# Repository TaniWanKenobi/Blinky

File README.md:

# Blinky Board

Made by **@Tanishq Goyal**

## What is the Blinky Board?

The Blinky Board is a colorful LED chaser that you can customize with your own PCB art! It uses:

- **NE555 Timer IC** in astable mode to generate clock pulses
- **CD4017 Decade Counter IC** to drive 10 LEDs in sequence
- Resistors, capacitors, and a potentiometer to control timing
- A custom PCB you design in **KiCad** and manufacture via **JLCPCB**

## How can I make my own Blinky Board?

I made this to teach people how to make a blinking circuit! It can be found [here](blinkyguide.md)

Assembly instructions can be found [here](https://blueprint.hackclub.com/resources/blinky-assembly)

Submit this at [Blueprint](https://blueprint.hackclub.com/)!

## 3D Model

## PCB

## Schematic

## Components Used

- **NE555P** – Timer IC  
- **CD4017** – Decade Counter IC  
- **Resistors** – 1kΩ, 470Ω  
- **Potentiometer (RV)** – Variable resistor for speed control  
- **Capacitors** – Electrolytic & ceramic  
- **LEDs** – 10 total (red, orange, yellow, emerald, blue)  

## License
This project is licensed under the CERN Open Hardware Licence Version 2 - Strongly Reciprocal. See the [LICENSE](LICENSE) file for details.

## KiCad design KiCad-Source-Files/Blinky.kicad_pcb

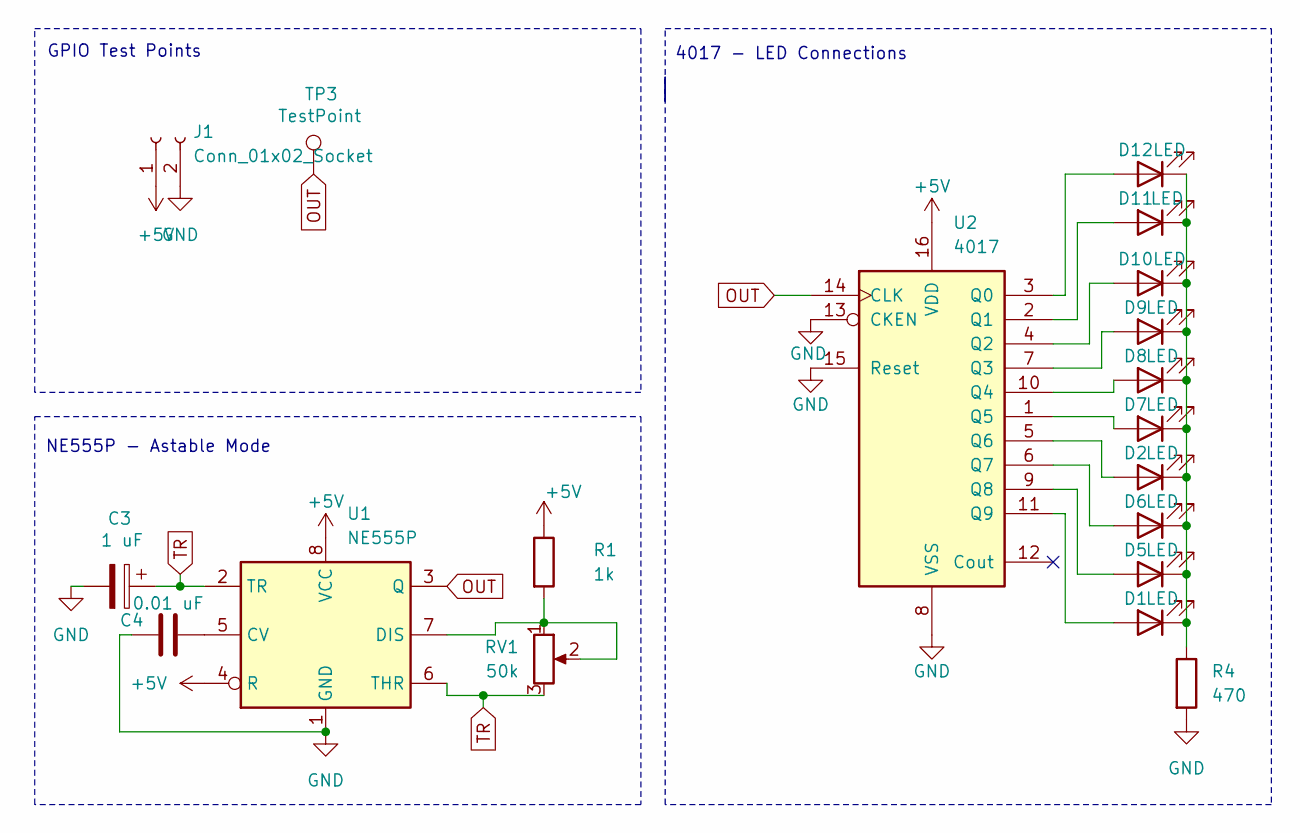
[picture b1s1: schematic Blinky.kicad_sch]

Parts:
C3: 1 uF; CP_Radial_D5.0mm_P2.00mm
C4: 0.01 uF; CP_Radial_D5.0mm_P2.00mm
D1, D2, D5, D6, D7, D8, D9, D10, D11, D12: LED; LED_D3.0mm
J1: Conn_01x02_Socket; PinHeader_1x02_P2.54mm_Vertical
R1: 1k; R_Axial_DIN0207_L6.3mm_D2.5mm_P7.62mm_Horizontal
R4: 470; R_Axial_DIN0207_L6.3mm_D2.5mm_P7.62mm_Horizontal
RV1: 50k; Potentiometer_Vishay_T93YA_Vertical
TP3: TestPoint; PinSocket_1x01_P2.54mm_Vertical
U1: NE555P; DIP-8_W7.62mm
U2: 4017; N16

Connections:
+5V: J1.1, R1.1, U1.4 (R), U1.8 (VCC), U2.16 (VDD)
GND: C3.2, C4.1, J1.2, R4.2, U1.1 (GND), U2.8 (VSS), U2.13 (CKEN), U2.15 (Reset)
unnamed: D1.2 (A), U2.11 (Q9)
unnamed: D1.1 (K), D2.1 (K), D5.1 (K), D6.1 (K), D7.1 (K), D8.1 (K), D9.1 (K), D10.1 (K), D11.1 (K), D12.1 (K), R4.1
unnamed: D2.2 (A), U2.5 (Q6)
unnamed: D5.2 (A), U2.9 (Q8)
unnamed: D6.2 (A), U2.6 (Q7)
unnamed: D7.2 (A), U2.1 (Q5)
unnamed: D8.2 (A), U2.10 (Q4)
unnamed: D9.2 (A), U2.7 (Q3)
unnamed: D10.2 (A), U2.4 (Q2)
unnamed: D11.2 (A), U2.2 (Q1)
unnamed: D12.2 (A), U2.3 (Q0)
unnamed: C4.2, U1.5 (CV)
unnamed: R1.2, RV1.1, RV1.2, U1.7 (DIS)
OUT: TP3.1, U1.3 (Q), U2.14 (CLK)
TR: C3.1, RV1.3, U1.2 (TR), U1.6 (THR)

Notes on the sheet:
GPIO Test Points
4017 - LED Connections
NE555P - Astable Mode

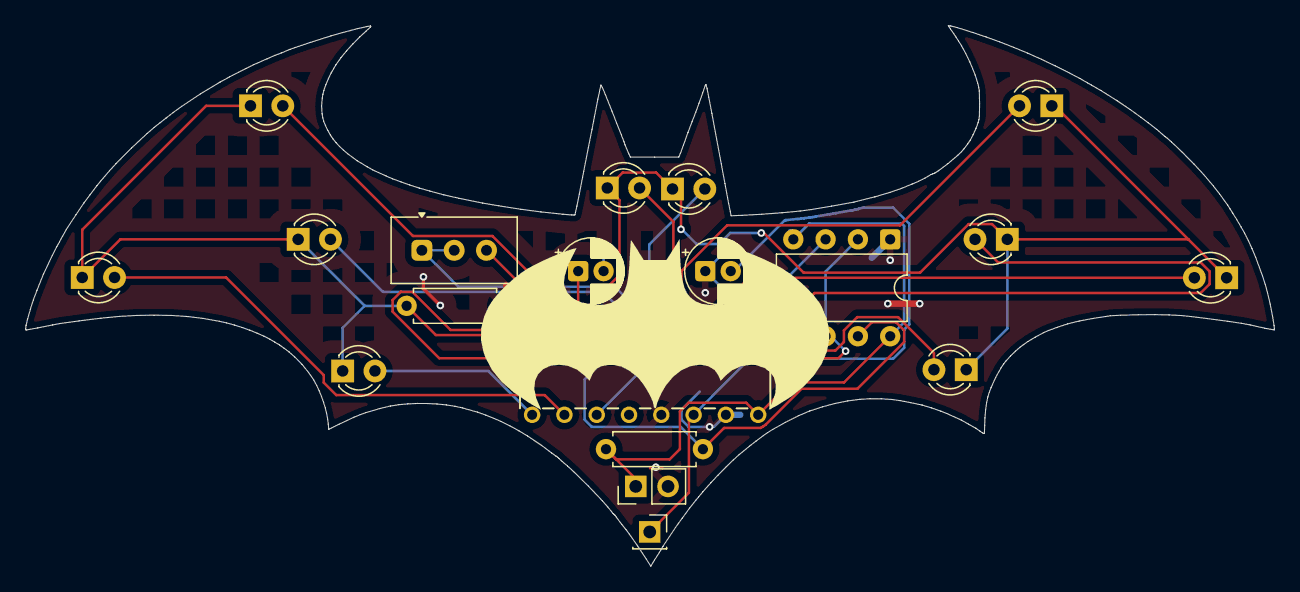
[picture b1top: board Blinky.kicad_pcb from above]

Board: 2 copper layers, 98.2 x 42.5 mm, 19 parts (0 on the bottom side), 17 nets.

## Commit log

2025-12-06 Add tutorial for building a 555 LED Chaser board
    This tutorial provides a comprehensive guide on building a 555 LED Chaser board, including setup, design, and submission processes.
2025-12-06 Document GPIO connection and resistor calculation
    Added instructions for connecting GPIO to LEDs and calculating resistor values.
2025-12-06 Clarify LED circuit parameters and resistor usage
    Added definitions for supply voltage, LED forward voltage, and desired current. Enhanced explanation of power-limiting resistors and their impact on LED brightness and component life.
2025-12-06 Improve LED connection instructions and resistor details
    Revised text for clarity and conciseness regarding LED connections and resistor values.
2025-12-07 Enhance guide with detailed wiring and KiCad instructions
    Expanded section on connecting components and clarified wiring instructions for LEDs and resistors. Added detailed steps for importing CD4017 footprint into KiCad.
2025-12-14 Update README with project description and link
    Added a brief description of the project and a link.
2025-12-14 Add readme and source files
2025-12-14 Revise wording in Blinky Board guide section
